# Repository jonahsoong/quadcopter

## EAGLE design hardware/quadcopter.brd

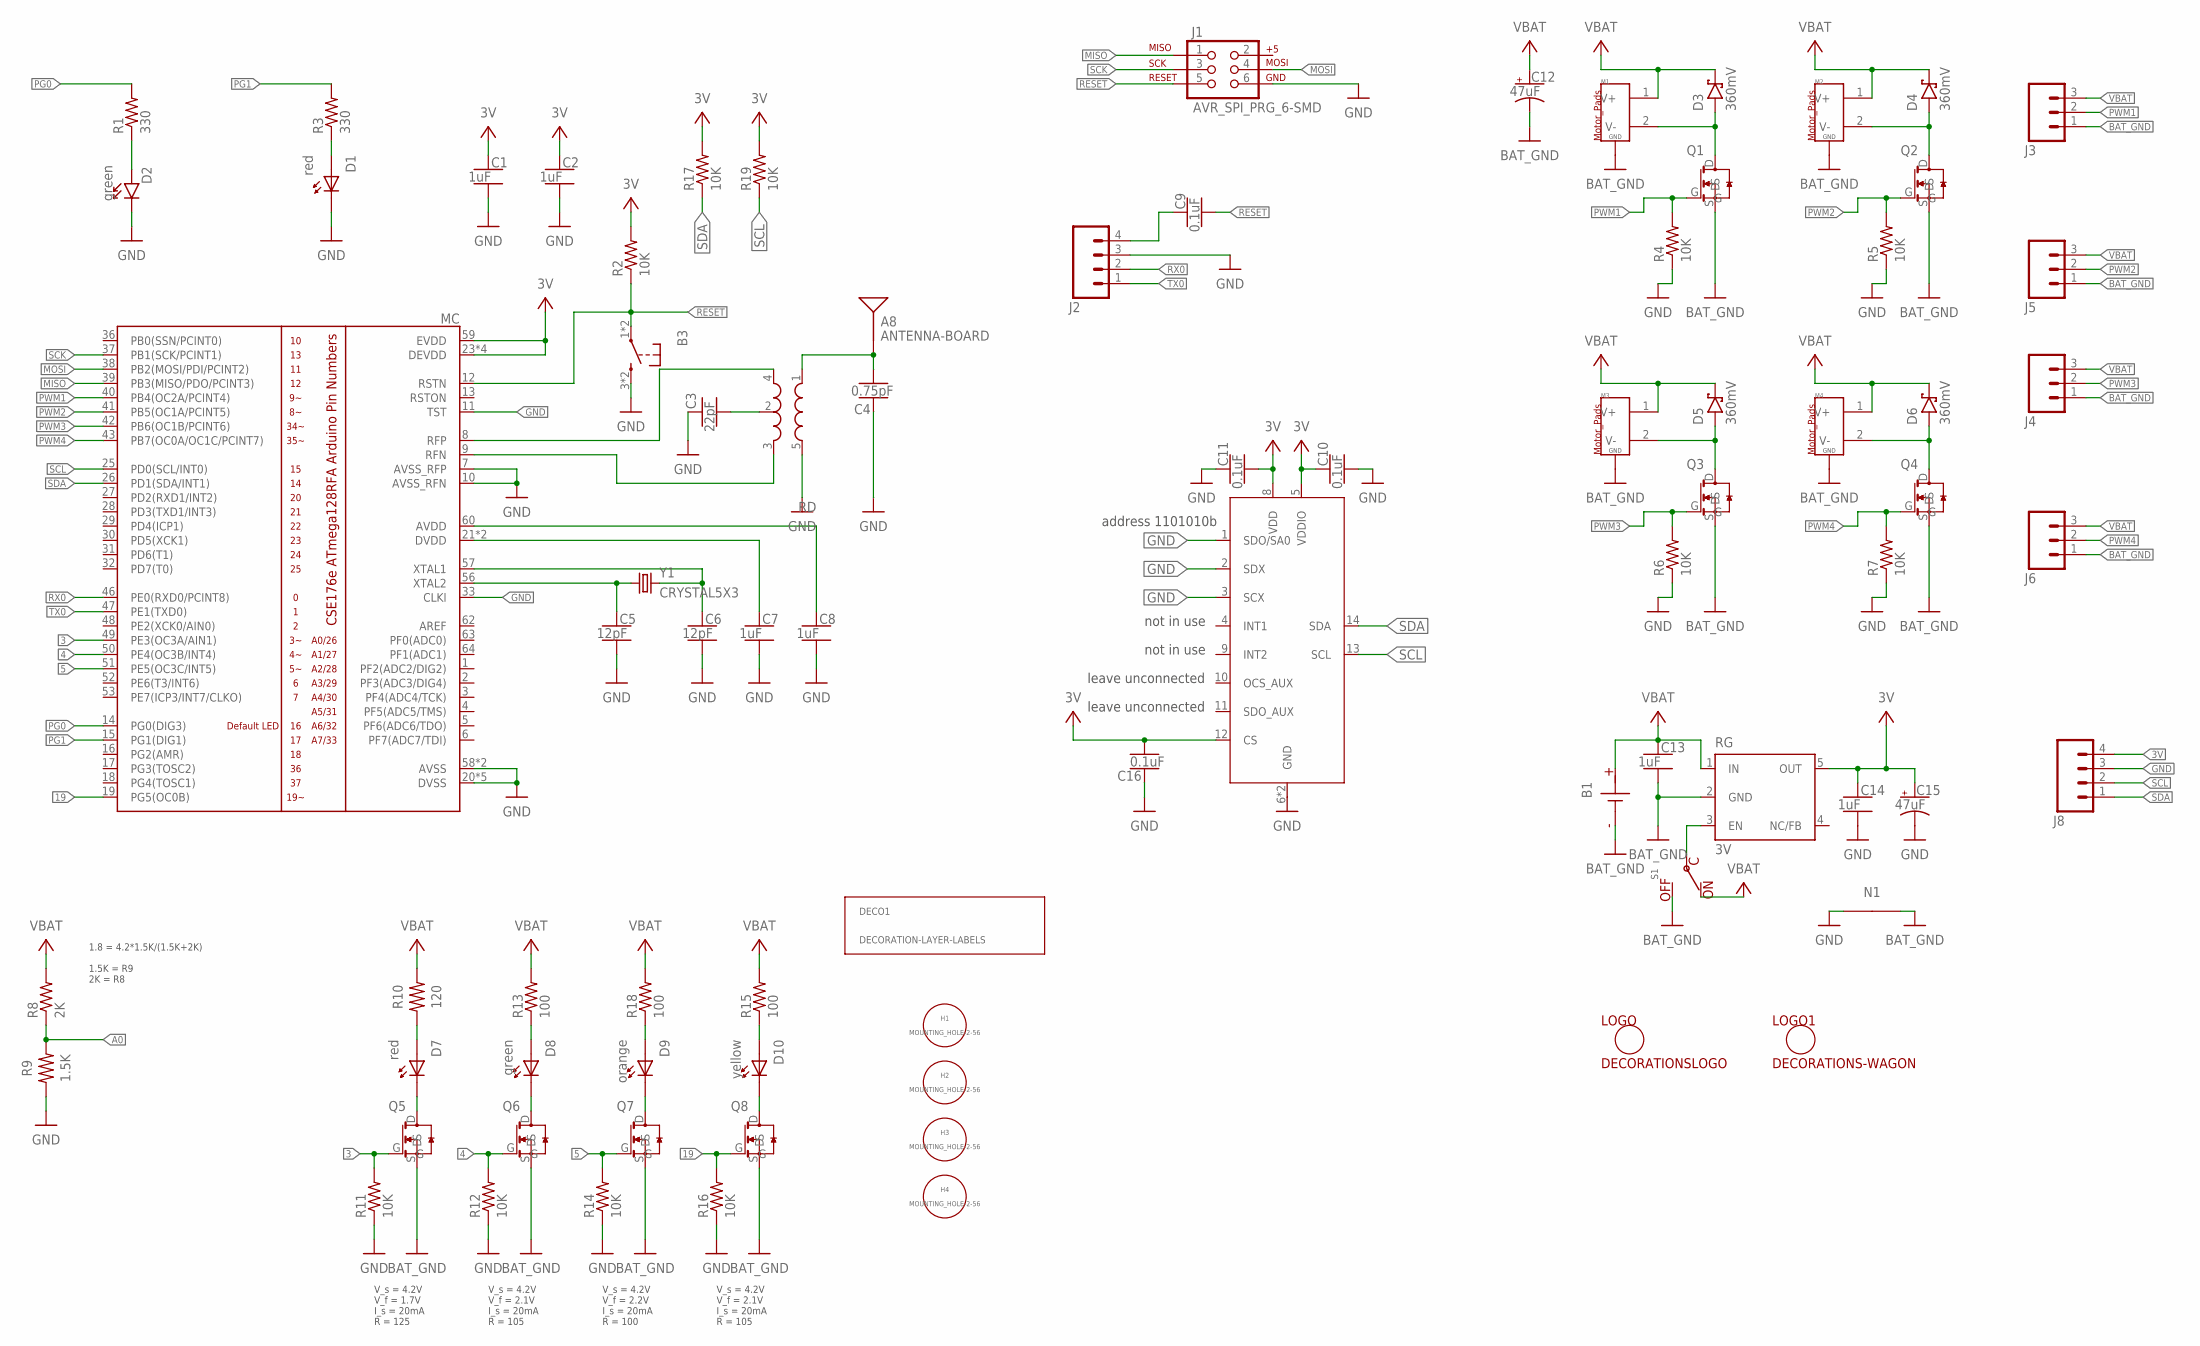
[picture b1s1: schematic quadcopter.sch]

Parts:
A8: ANTENNA-BOARD; ANT_PCB_2.4GHZ_NRF8001_1.6MM_1OZ
B1: BATTERY-SCREW-TERMINAL; SCREW-TERMINAL-1X2-2.54MM
B3: PUSHBUTTON_SMD-VERTICAL-1; TE_FSM8JSMA_HS
C1, C2, C7, C8, C13, C14: 1uF; CAPC2012X140_HS
C3: 22pF; CAPC2012X140_HS
C4: 0.75pF; CAPC2012X140_HS
C5, C6: 12pF; CAPC2012X140_HS
C9, C10, C11, C16: 0.1uF; CAPC2012X140_HS
C12, C15: 47uF; CAPMP3216X180
D1, D7: red; 0805_LED
D2: green; LEDSC125X200X120-2_HS
D3, D4, D5, D6: 360mV; SODFL3516X96
D8: green; 0805_LED
D9: orange; 0805_LED
D10: yellow; 0805_LED
DECO1: DECORATION-LAYER-LABELS; LAYER_LABELS
H1, H2, H3, H4: MOUNTING_HOLE-2-56; 2-56-MOUNTING-HOLE-NO-METAL
IM: LSM_IMU-LGA-14L-6AXIS; IMU_LSM6DS0X
J1: AVR_SPI_PRG_6-SMD; 2X3-SMD
J2: HEADER-4POS-0.1IN-FEMALE-SMD-BOTTOM-ENTRY; HEADER-1X4-BOTTOM-ENTRY
J3, J4, J5, J6: HEADER-0.1IN-3POS; HDRVR3W80P254_1X3_812X254X850B
J8: HEADER-4POS-0.1IN-FEMALE; HDRVR4W80P254_1X4_1066X254X850B
LOGO: DECORATIONSLOGO; LOGO
LOGO1: DECORATIONS-WAGON; WAGON
M1, M2, M3, M4: MOTOR_PADS_GND-MOLEX-SMD; MOLEX-0532610271
MC: ATMEGA128RFA1; QFN-64
N1: NET_BRIDGE-NETTONET; NET_BRIDGE
Q1, Q2, Q3, Q4, Q5, Q6, Q7, Q8: MOSFET-SOT-23-NMOSFET; SOT23-3-NMOSFET
R1, R3: 330; RESC2012X60_HS
R2, R4, R5, R6, R7, R11, R12, R14, R16, R17, R19: 10K; RESC2012X60_HS
R8: 2K; RESC2012X60_HS
R9: 1.5K; 0805_RESISTOR
R10: 120; 0805_RESISTOR
R13, R15, R18: 100; RESC2012X60_HS
RD: BALUN0805; BALUN
RG: 3V; SOT23-DBV
S1: POWER-SWITCH-MFS201N-9-Z-SMD-EDGE; JS102011SAQN
Y1: CRYSTAL5X3; CRYSTAL-SMD-5X3

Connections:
3: MC.49 (PE3(OC3A/AIN1)), Q5.G, R11.2
3V: C1.1, C2.1, C10.1, C11.2, C14.1, C15.1 (+), C16.2, IM.5 (VDDIO), IM.8 (VDD), IM.12 (CS), J8.4, MC.23 (DEVDD), MC.34 (DEVDD), MC.44 (DEVDD), MC.54 (DEVDD), MC.59 (EVDD), R2.2, R17.2, R19.2, RG.5 (OUT)
4: MC.50 (PE4(OC3B/INT4)), Q6.G, R12.2
5: MC.51 (PE5(OC3C/INT5)), Q7.G, R14.2
19: MC.19 (PG5(OC0B)), Q8.G, R16.2
A0: R8.1, R9.2
BAT_GND: B1.1 (N), C12.2 (-), C13.2, J3.1, J4.1, J5.1, J6.1, M1.G1 (GND), M1.G2 (GND), M2.G1 (GND), M2.G2 (GND), M3.G1 (GND), M3.G2 (GND), M4.G1 (GND), M4.G2 (GND), N1.1, Q1.S, Q2.S, Q3.S, Q4.S, Q5.S, Q6.S, Q7.S, Q8.S, RG.2 (GND), S1.A (OFF)
GND: B3.3 (2), B3.4 (2), C1.2, C2.2, C3.1, C4.1, C5.2, C6.2, C7.2, C8.2, C10.2, C11.1, C14.2, C15.2 (-), C16.1, D1.C, D2.C, IM.1 (SDO/SA0), IM.2 (SDX), IM.3 (SCX), IM.6 (GND), IM.7 (GND), J1.6, J2.3, J8.3, MC.7 (AVSS_RFP), MC.10 (AVSS_RFN), MC.11 (TST), MC.20 (DVSS), MC.24 (DVSS), MC.33 (CLKI), MC.35 (DVSS), MC.45 (DVSS), MC.55 (DVSS), MC.58 (AVSS), MC.61 (AVSS), N1.2, R4.1, R5.1, R6.1, R7.1, R9.1, R11.1, R12.1, R14.1, R16.1, RD.5 (GND)
MISO: J1.1, MC.39 (PB3(MISO/PDO/PCINT3))
MOSI: J1.4, MC.38 (PB2(MOSI/PDI/PCINT2))
unnamed: D1.A, R3.1
unnamed: C9.1, J2.4
unnamed: C3.2, RD.2 (GND)
unnamed: MC.8 (RFP), RD.4 (OUT1)
unnamed: MC.9 (RFN), RD.3 (OUT2)
unnamed: A8.FEED, C4.2, RD.1 (IN)
unnamed: C8.1, MC.60 (AVDD)
unnamed: C7.1, MC.21 (DVDD), MC.22 (DVDD)
unnamed: C6.1, MC.57 (XTAL1), Y1.3 (2)
unnamed: C5.1, MC.56 (XTAL2), Y1.1
unnamed: D2.A, R1.1
unnamed: D3.2 (A), M1.2 (V-), Q1.D
unnamed: D4.2 (A), M2.2 (V-), Q2.D
unnamed: D5.2 (A), M3.2 (V-), Q3.D
unnamed: D6.2 (A), M4.2 (V-), Q4.D
unnamed: RG.3 (EN), S1.C
unnamed: D7.C, Q5.D
unnamed: D7.A, R10.1
unnamed: D8.C, Q6.D
unnamed: D8.A, R13.1
unnamed: D9.C, Q7.D
unnamed: D9.A, R18.1
unnamed: D10.C, Q8.D
unnamed: D10.A, R15.1
PG0: MC.14 (PG0(DIG3)), R1.2
PG1: MC.15 (PG1(DIG1)), R3.2
PWM1: J3.2, MC.40 (PB4(OC2A/PCINT4)), Q1.G, R4.2
PWM2: J5.2, MC.41 (PB5(OC1A/PCINT5)), Q2.G, R5.2
PWM3: J4.2, MC.42 (PB6(OC1B/PCINT6)), Q3.G, R6.2
PWM4: J6.2, MC.43 (PB7(OC0A/OC1C/PCINT7)), Q4.G, R7.2
RESET: B3.1, B3.2 (1), C9.2, J1.5, MC.12 (RSTN), R2.1
RX0: J2.2, MC.46 (PE0(RXD0/PCINT8))
SCK: J1.3, MC.37 (PB1(SCK/PCINT1))
SCL: IM.13 (SCL), J8.2, MC.25 (PD0(SCL/INT0)), R19.1
SDA: IM.14 (SDA), J8.1, MC.26 (PD1(SDA/INT1)), R17.1
TX0: J2.1, MC.47 (PE1(TXD0))
VBAT: B1.2, C12.1 (+), C13.1, D3.1 (C), D4.1 (C), D5.1 (C), D6.1 (C), J3.3, J4.3, J5.3, J6.3, M1.1 (V+), M2.1 (V+), M3.1 (V+), M4.1 (V+), R8.2, R10.2, R13.2, R15.2, R18.2, RG.1 (IN), S1.B (ON)

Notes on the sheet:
address 1101010b
not in use
leave unconnected
1.8 = 4.2*1.5K/(1.5K+2K) 1.5K = R9 2K = R8
V_s = 4.2V V_f = 1.7V I_s = 20mA R = 125
V_s = 4.2V V_f = 2.1V I_s = 20mA R = 105
V_s = 4.2V V_f = 2.2V I_s = 20mA R = 100

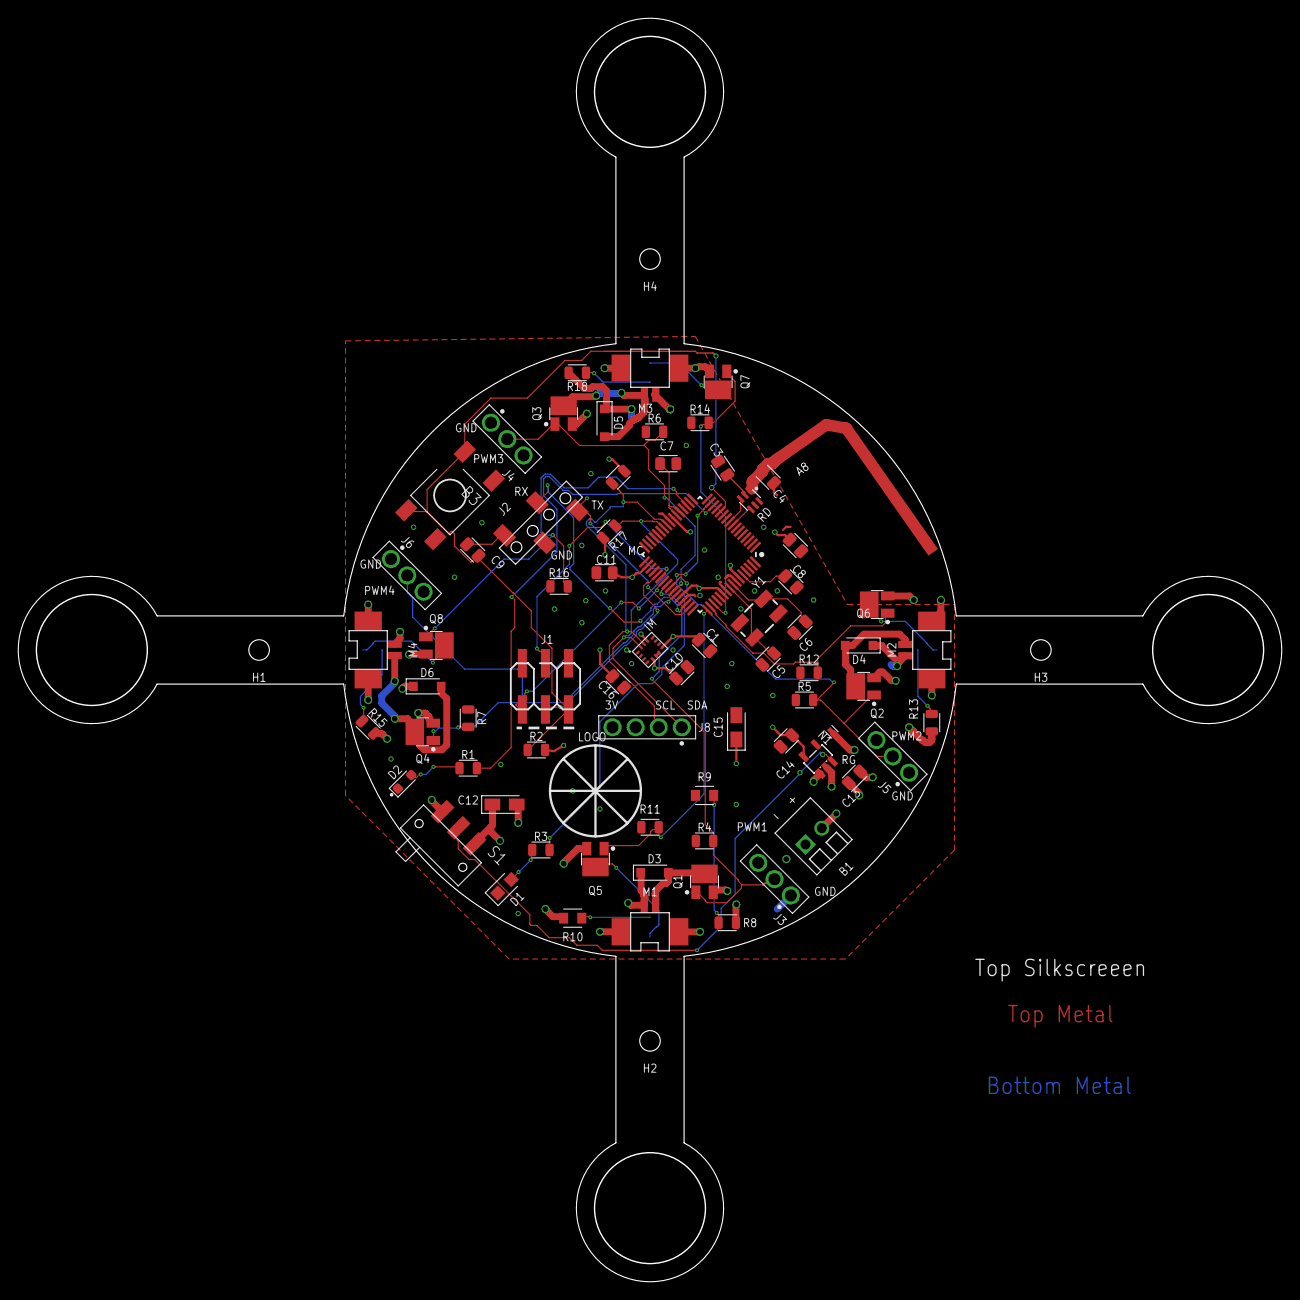
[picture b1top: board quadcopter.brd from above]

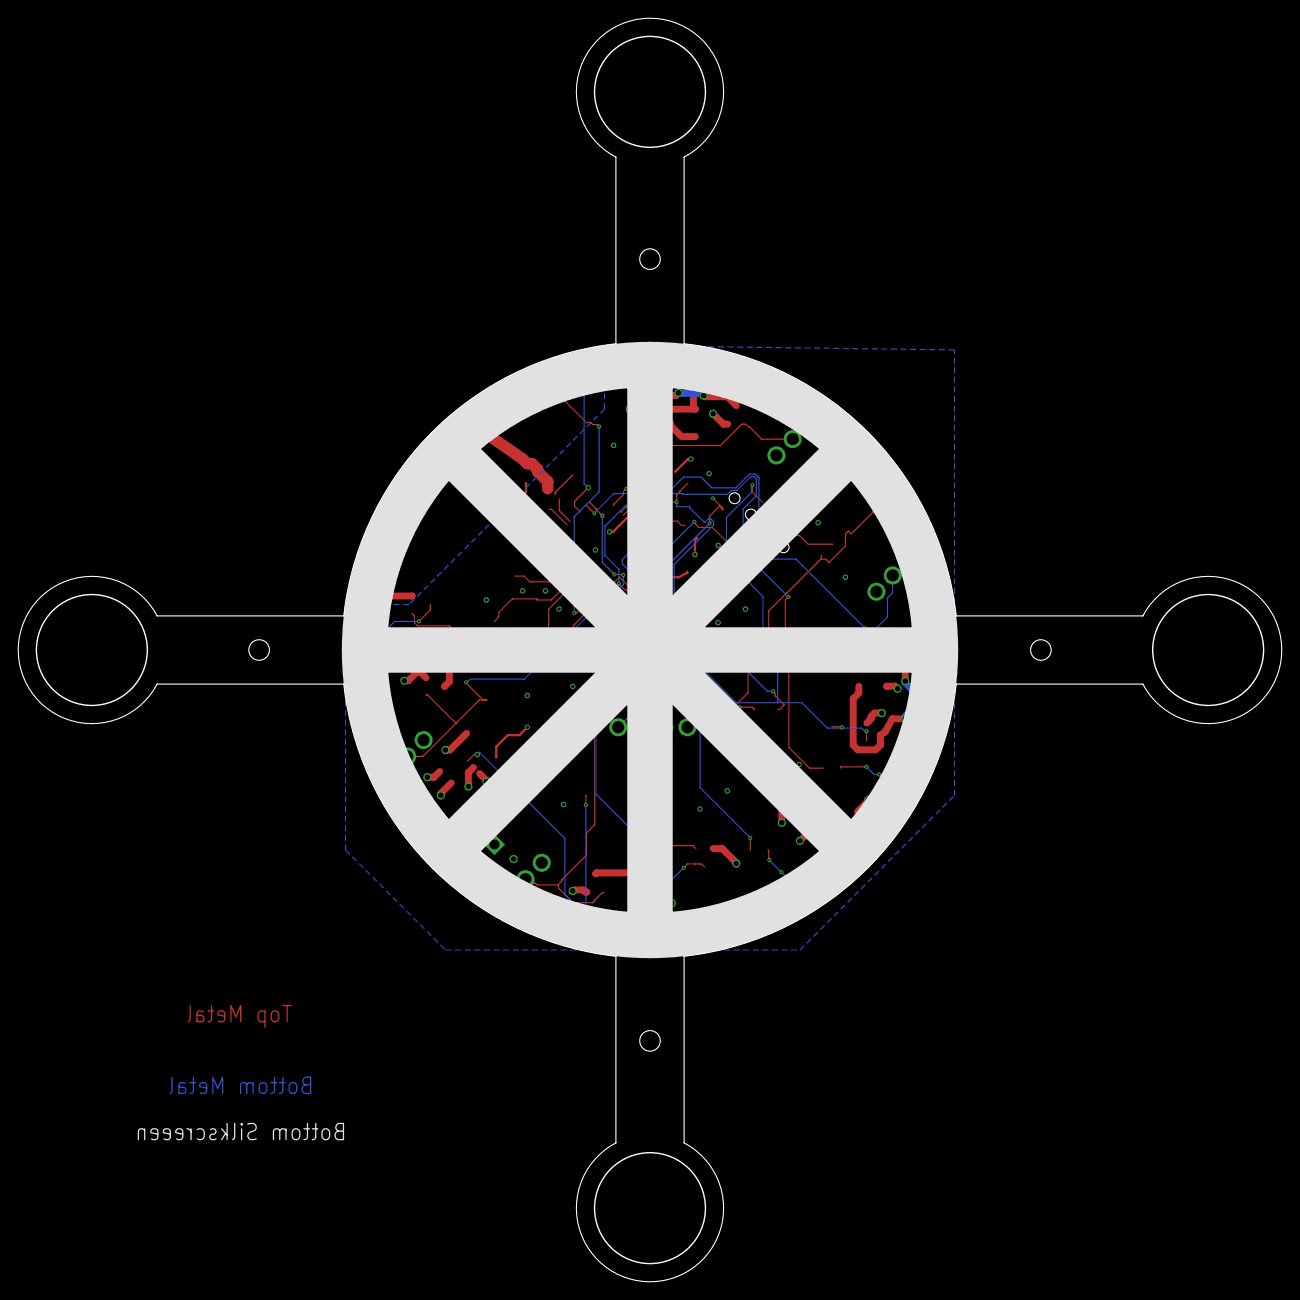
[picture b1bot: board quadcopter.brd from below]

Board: 4 copper layers, 139.0 x 139.0 mm, 81 parts (5 on the bottom side), 47 nets.

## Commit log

2023-11-27 quadcopter code
